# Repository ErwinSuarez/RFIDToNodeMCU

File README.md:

# RFIDToNodeMCU
Connection of NodeMCU to RFID-RC522
This is to connect RFID-RC522 to NodeMCU with the Use of Arduino IDE
Arduino IDE is used to display the response value from server
Raspberry Pi3 is being used as a web server.

The way this work is MFRC522 reads the RFID tag, 
NodeMCU collects this data and sends this data through a web server
The web server then recieves this data and records this into servers 
database. The server should have responded to clients request and
returns a boolean value of true or false depending on the RFID tag

NOTE: THIS IS STILL IN DEVELOPMENT. goal is index.php should be used
to respond to clients request with data being passed still need to 
html script to recieve servers reposnse

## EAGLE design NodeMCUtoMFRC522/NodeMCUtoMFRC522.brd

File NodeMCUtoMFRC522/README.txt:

This is a conenction board from MFRC522 to NodeMCU

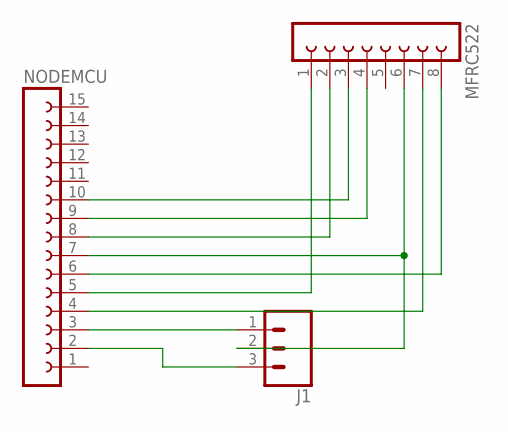
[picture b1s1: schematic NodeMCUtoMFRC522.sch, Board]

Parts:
J1: CONN_03POLAR; MOLEX-1X3
MFRC522: FE08-1; FE08
NODEMCU: FE15-1; FE15

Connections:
unnamed: MFRC522.7, NODEMCU.4
unnamed: MFRC522.1, NODEMCU.5
unnamed: MFRC522.8, NODEMCU.6
unnamed: J1.2, MFRC522.6, NODEMCU.7
unnamed: MFRC522.2, NODEMCU.8
unnamed: MFRC522.4, NODEMCU.9
unnamed: MFRC522.3, NODEMCU.10
unnamed: J1.1, NODEMCU.3
unnamed: J1.3, NODEMCU.2

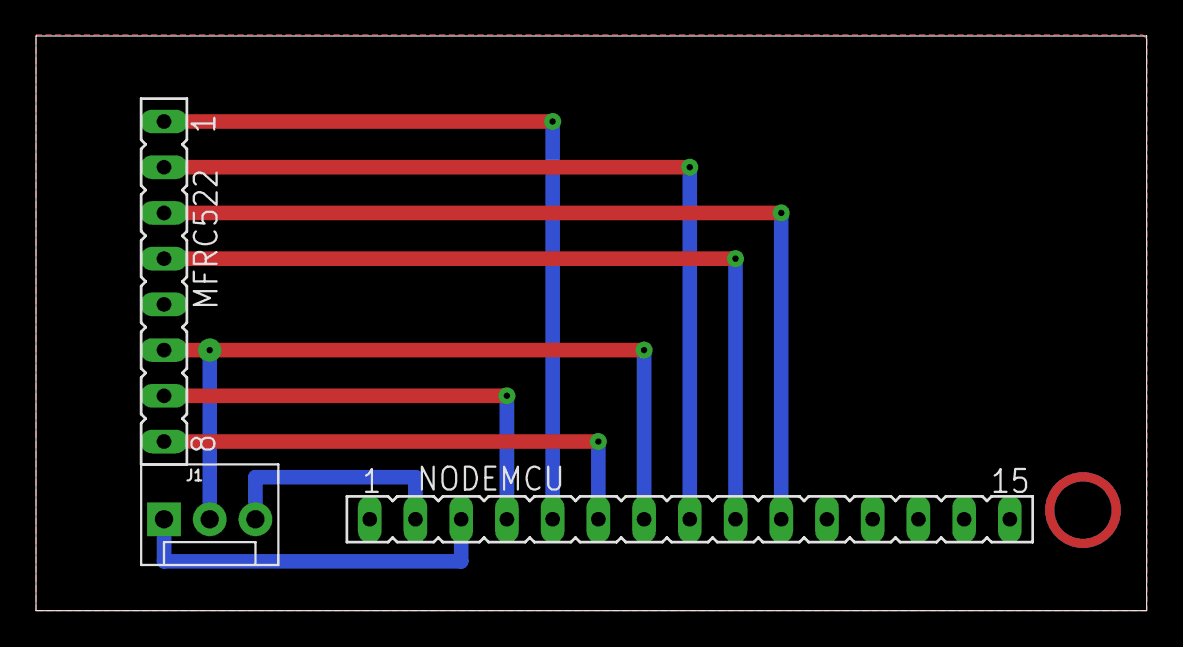
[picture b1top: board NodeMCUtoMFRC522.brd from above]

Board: 2 copper layers, 61.7 x 31.9 mm, 3 parts (0 on the bottom side), 9 nets.

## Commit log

2018-05-31 Create NodeMCUMFRC522.ino
    Copied file from work space
2018-05-31 Create NodeMCUServer
    Copied file to make NodeMCU as a sample server
2018-05-31 Create NodeMCUMFRC522WebClient
    Copied file from work space
    This will display response in Arduino IDE Serial Monitor
2018-05-31 Add files via upload
    Added file to be placed into server STILL in development
2018-06-01 Rename NodeMCUMFRC522WebClient to NodeMCUMFRC522WebClient.ino
    changed file name extension
2018-06-01 Rename NodeMCUServer to NodeMCUServer.ino
    changed file name
2018-06-01 Update README.md
    Still in progress
2018-06-01 Create README.txt
    PCB design
2018-06-01 Add files via upload
    PCB files uploaded

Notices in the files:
parts and their libraries:
SparkFun-Connectors: Licensing: Creative Commons ShareAlike 4.0 International - https://creativecommons.org/licenses/by-sa/4.0
